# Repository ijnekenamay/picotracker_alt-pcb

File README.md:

# Picotracker Alt-PCB

~~**Do not fabricate! There could be a major mistake around MIDI!!**~~

**[Alex fixed it!](https://github.com/ijnekenamay/picotracker_alt-pcb/pull/2) We should be able to go ahead with production now.**

This project is about [democloid picoTracker's](https://github.com/democloid/picoTracker/) alternative PCB.
Inexpensive handheld devices can be built to run LittleGPTracker(a.k.a piggytracker).
It basically follows the original DIY version, with a few modifications of my own. They are described below.

[You can see it in motion here.](https://www.instagram.com/p/C2BvngaruZN/?utm_source=ig_web_copy_link&igsh=MzRlODBiNWFlZA==)

## Feature

- The two PCBs act as an enclosure by sandwiching the components together.
- I wanted a module for the charging function and plenty of memory, so I went with the [Pimoroni Pico LiPo](https://shop.pimoroni.com/products/pimoroni-pico-lipo).
- I wanted a micro-speaker like the DirtywaveM8, so I added one... and a Class D amplifier module.
- A speaker kill switch has been added.
- This also uses Kailh Choc V1 for the keycaps because of my personal taste.
- You can change any specification by yourself if you have access to Kicad.
- [See image for values of components around MIDI.](https://raw.githubusercontent.com/ijnekenamay/picotracker_alt-pcb/main/images/MIDI_resistor_value.jpg)
- I designed a back panel that could be output with a 3D printer because I felt the microspeaker needed box resonance. Also, if you would like to try it, please see the STL data. Feedback is welcome.
- 

## BOM

| Value                                             | Quantity | info                                                                                                                           |
| ------------------------------------------------- | -------- | ------------------------------------------------------------------------------------------------------------------------------ |
| Pimoroni Pico LiPo 16MB                           | 1        | [URL](https://shop.pimoroni.com/products/pimoroni-pico-lipo)　 [URL(Japan only)](https://akizukidenshi.com/catalog/g/g116997/) |
| ILI9341 3.2" display                              | 1        | [URL](https://www.aliexpress.us/item/3256802819098352.html)                                                                    |
| GY-PCM5102 DAC module                             | 1        | [URL](https://www.aliexpress.us/item/3256802711963831.html)                                                                    |
| Adafruit Micro SD SPI or SDIO Card Breakout Board | 1        | [URL](https://www.adafruit.com/product/4682)                                                                                   |
| Kailh Choc V1 key switch                          | 9        |                                                                                                                                |
| keycaps                                           | 9        |                                                                                                                                |
| max98306 class D amp                              | 1        | [URL](https://ja.aliexpress.com/item/1005004990814956.html)                                                                    |
| Micro speaker                                     | 2        | [URL](https://akizukidenshi.com/catalog/g/gP-12494/)                                                                           |
| SMD Slide Switch                                  | 1        | on-on [The footprint uses a 6-pin one.](https://akizukidenshi.com/download/ds/switronic/IS-2245S-G.PDF)                        |
| PJ-311 3.5mm Stereo Jack                          | 2        |                                                                                                                                |
| 1n4148                                            | 1        | SOD-323                                                                                                                        |
| 47R                                               | 2        | 1608                                                                                                                           |
| 220R                                              | 1        | 1608                                                                                                                           |
| 470R                                              | 1        | 1608                                                                                                                           |
| 10k                                               | 1        | 1608                                                                                                                           |
| 6N138                                             | 1        | DIP-8 SMD(Just cut off the normal DIP8 leg.)                                                                                   |
| lipo battery                                      | 1        | I use 1200mAh and need less recharging.                                                                                        |
| other                                             | \*       | Other pin headers and sockets. We need standoff bolts, nuts, screws, and lots of them.                                         |

It is recommended to use short pin headers and to solder directly without using sockets. At the very least, the effective depth of the 3D printer back panel is only 11 mm, which would interfere with the use of pin sockets. (but i wanted to go thin)

The images below are prototype versions and differ from the actual data.

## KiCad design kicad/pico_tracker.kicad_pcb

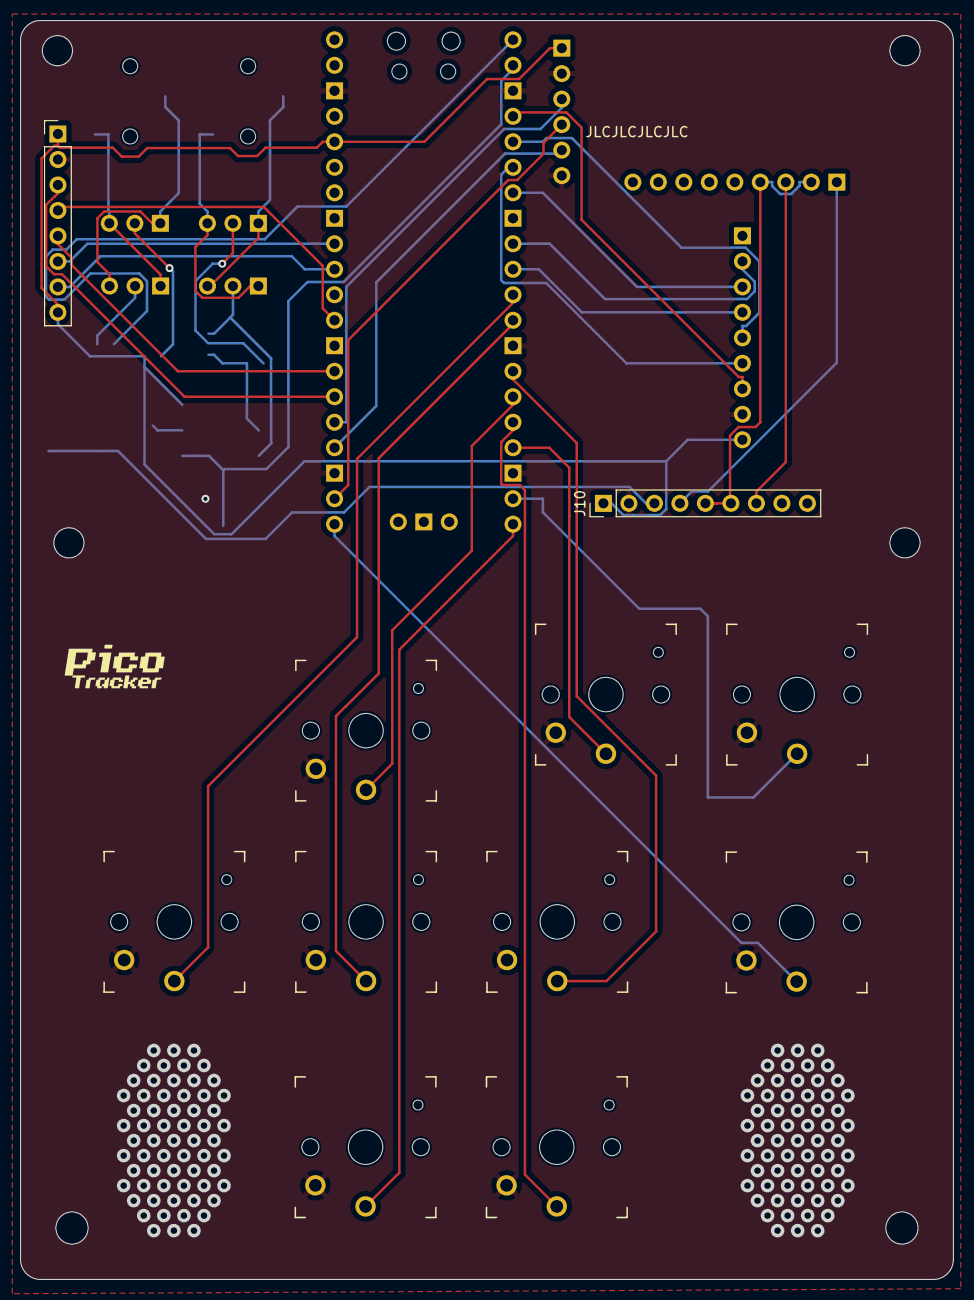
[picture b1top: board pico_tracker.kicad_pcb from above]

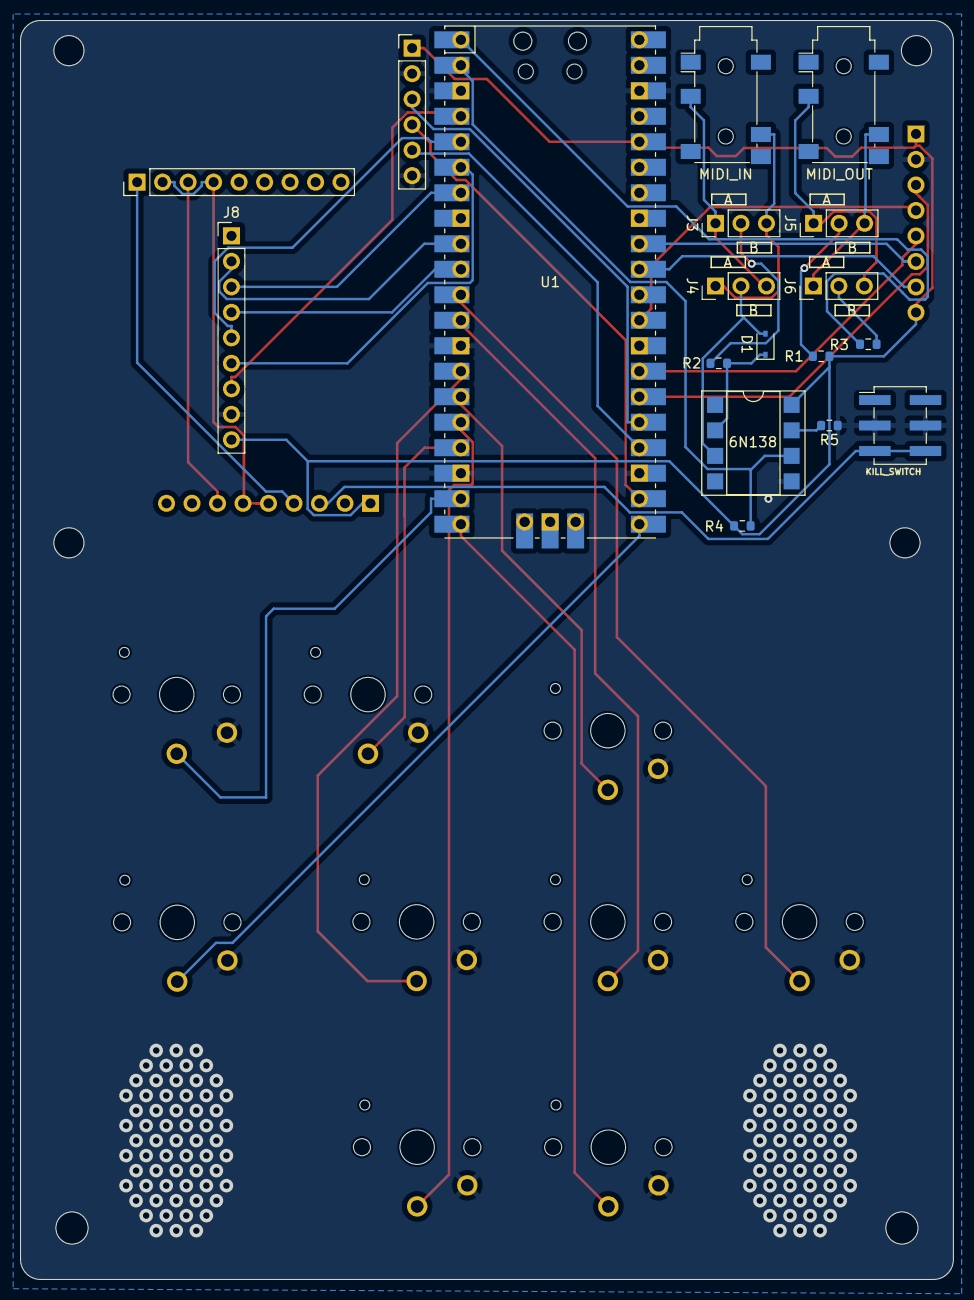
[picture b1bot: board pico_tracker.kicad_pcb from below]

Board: 2 copper layers, 92.9 x 125.4 mm, 30 parts (18 on the bottom side), 41 nets.

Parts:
D1: 1n4148; D_SOD-323
G1: LOGO; logo_silk
J1: MIDI_OUT; Jack_3.5mm_PJ311_Horizontal
J2: MIDI_IN; Jack_3.5mm_PJ311_Horizontal
J3: MIDI_IN_A_B_VCC; PinHeader_1x03_P2.54mm_Vertical
J4: MIDI_IN_A_B_DATA; PinHeader_1x03_P2.54mm_Vertical
J5: MIDI_OUT_A_B_VCC; PinHeader_1x03_P2.54mm_Vertical
J6: MIDI_OUT_A_B_DATA; PinHeader_1x03_P2.54mm_Vertical
J7: DISPLAY; PinHeader_1x08_P2.54mm_Vertical
J8: SDCARD; PinHeader_1x09_P2.54mm_Vertical
J9: KILL_SWITCH; PinHeader_2x03_P2.54mm_Vertical_SMD
J10: DclassAMP; PinHeader_1x09_P2.54mm_Vertical
R1, R3: 47R; R_0603_1608Metric
R2: 220R; R_0603_1608Metric
R4: 470R; R_0603_1608Metric
R5: 10k; R_0603_1608Metric
REF1: PinHeader_1x09_P2.54mm_Vertical_SMD_Pin1Left; PinHeader_1x09_P2.54mm_Vertical
SW1, SW2, SW3, SW4, SW5, SW6, SW7, SW8, SW9: SW_PG1350
U1: Pico; RPi_Pico_SMD_TH
U2: 6N138; DIP-8_W7.62mm_SMDSocket_SmallPads
U3: PCM5102_Module; PinHeader_1x06_P2.54mm_Vertical

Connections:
A: SW7.1, U1.19 (GPIO14)
AGND: J10.5, J10.6, REF1.2, REF1.4
B: SW6.1, U1.17 (GPIO13)
BCK: U1.24 (GPIO18), U3.5 (BCK)
CLK: J8.7, U1.4 (GPIO2)
D1: J8.3, U1.7 (GPIO5)
D3: J8.4, U1.10 (GPIO7)
DAT2: J8.2, U1.9 (GPIO6)
DIN: U1.22 (GPIO17), U3.4 (DIN)
DOWN: SW2.1, U1.12 (GPIO9)
DP3: J7.3, U1.26 (GPIO20)
DP4: J7.4, U1.29 (GPIO22)
DP5: J7.5, U1.27 (GPIO21)
DP6: J7.6, U1.32 (GPIO27_ADC1)
DP7: J7.7, U1.31 (GPIO26_ADC0)
GND: J7.2, J8.8, J9.2, J9.5, J10.2, R5.1, SW1.2, SW2.2, SW3.2, SW4.2, SW5.2, SW6.2, SW7.2, SW8.2, SW9.2, U1.3 (GND), U1.13 (GND), U1.18 (GND), U1.23 (GND), U1.38 (GND), U2.5 (GND), U3.2 (GND), U3.6 (SCK)
KILL_SWITCH: J9.1, J9.4, J10.3
LEFT: SW1.1, U1.11 (GPIO8)
LRCK: U1.25 (GPIO19), U3.3 (LRCK)
LT: SW8.1, U1.20 (GPIO15)
L_AMP: J10.4, REF1.1
unnamed: D1.2 (A), J4.2, U2.3 (C2)
unnamed: D1.1 (K), R2.2, U2.2 (C1)
unnamed: J3.1, J4.3
unnamed: J3.2, R2.1
unnamed: J3.3, J4.1
unnamed: J5.1, J6.3
unnamed: J5.2, R1.2
unnamed: J5.3, J6.1
unnamed: J6.2, R3.2
unnamed: R5.2, U2.7 (VO1)
PLAY: SW9.1, U1.21 (GPIO16)
RIGHT: SW3.1, U1.14 (GPIO10)
RT: SW5.1, U1.16 (GPIO12)
RX: R4.1, U1.2 (GPIO1), U2.6 (VO2)
R_AMP: J10.7, REF1.3
SI: J8.5, U1.5 (GPIO3)
SO: J8.6, U1.6 (GPIO4)
TX: R3.1, U1.1 (GPIO0)
UP: SW4.1, U1.15 (GPIO11)
VCC: J7.1, J7.8, J8.9, J10.1, R1.1, R4.2, U1.36 (3V3), U2.8 (VCC), U3.1 (VIN)

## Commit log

2026-03-06 fix: 6N138 VCC connexion and RX/TX pins flip
2026-03-06 chore: generate gerber files
2026-03-06 fix: add 10k resistor to pin 7
2026-03-06 docs: adds 10k resistor to readme
2026-03-06 chore: update gerber_main zip file
2026-03-23 thanks alex.
